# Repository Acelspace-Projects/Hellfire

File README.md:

<h1 align="center">
    <br>
    
    <br>
    <b>Hellfire</b>
</h3>

<h3 align="center">
    Ceci est un dépot pour le projet Hellfire utilisé pour le versionning et pour avoir des backups.
</h3>

<div class="badges" align="center">

</div>

---

### Description
Hellfire est un projet du club Acelspace.

### Liens
- [StabTraj](https://github.com/Acelspace-Projects/Hellfire/blob/main/Documentation/StabTraj/ST-(StabTraj)_Hellfire.xlsx)
- [Dossier de définition](https://github.com/Acelspace-Projects/Hellfire/blob/main/Documentation/DossierDeDefinition/DDD_Hellfire.pdf)
- [Dossier technique](https://github.com/Acelspace-Projects/Hellfire/blob/main/Documentation/DossierTechnique/DT_Hellfire.pdf)

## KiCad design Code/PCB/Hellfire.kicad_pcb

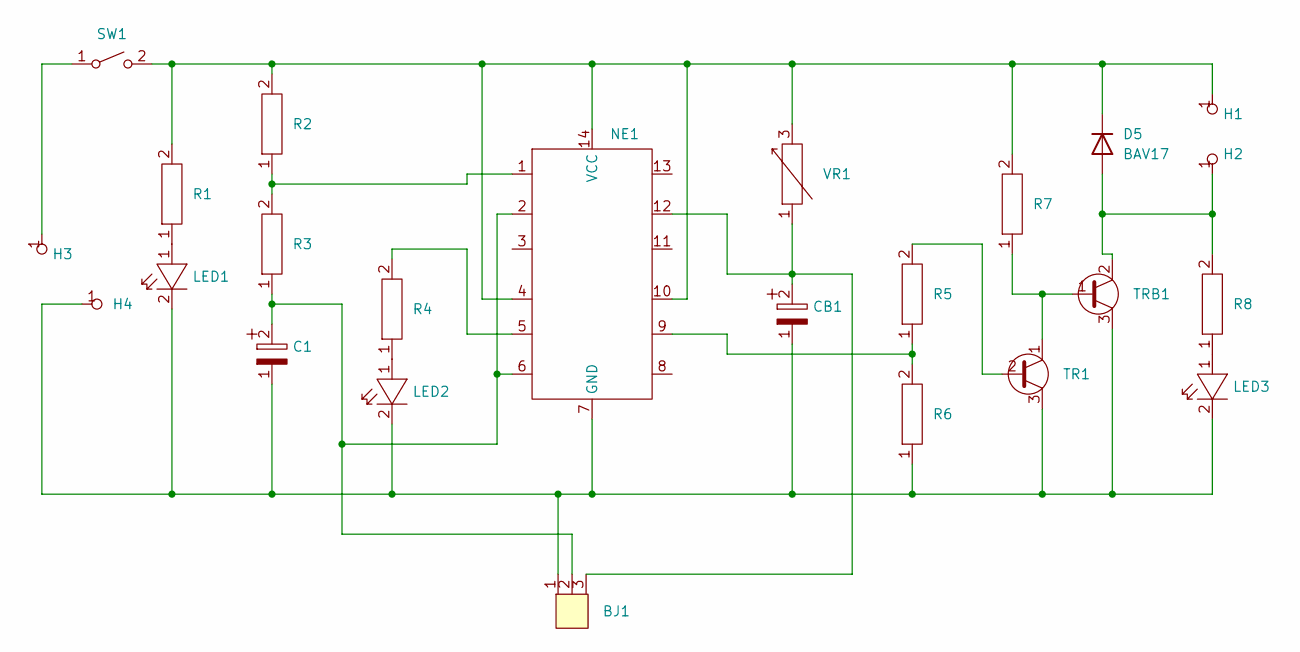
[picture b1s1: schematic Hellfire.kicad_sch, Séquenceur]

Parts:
BJ1: Jack
C1: Capacitor
CB1: Capacitor Big
D5: BAV17; D_DO-35_SOD27_P7.62mm_Horizontal
H1, H2, H3, H4: Via
LED1, LED2, LED3: LED
NE1: NE556
R1, R2, R3, R4, R5, R6, R7, R8: Resistor
SW1: Switch
TR1: Transistor
TRB1: Transistor Big
VR1: Variable Resistor

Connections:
unnamed: BJ1.2, C1.2, NE1.2, NE1.6, R3.1
unnamed: BJ1.3, CB1.2, NE1.12, VR1.1
unnamed: D5.2 (A), H2.1, R8.2, TRB1.2
unnamed: D5.1 (K), H1.1, NE1.4, NE1.10, NE1.14 (VCC), R1.2, R2.2, R7.2, SW1.2, VR1.3
unnamed: H3.1, SW1.1
unnamed: LED1.1, R1.1
unnamed: LED2.1, R4.1
unnamed: LED3.1, R8.1
unnamed: BJ1.1, C1.1, CB1.1, H4.1, LED1.2, LED2.2, LED3.2, NE1.7 (GND), R6.1, TR1.3, TRB1.3
unnamed: NE1.1, R2.1, R3.2
unnamed: NE1.5, R4.2
unnamed: NE1.9, R5.1, R6.2
unnamed: R5.2, TR1.2
unnamed: R7.1, TR1.1, TRB1.1

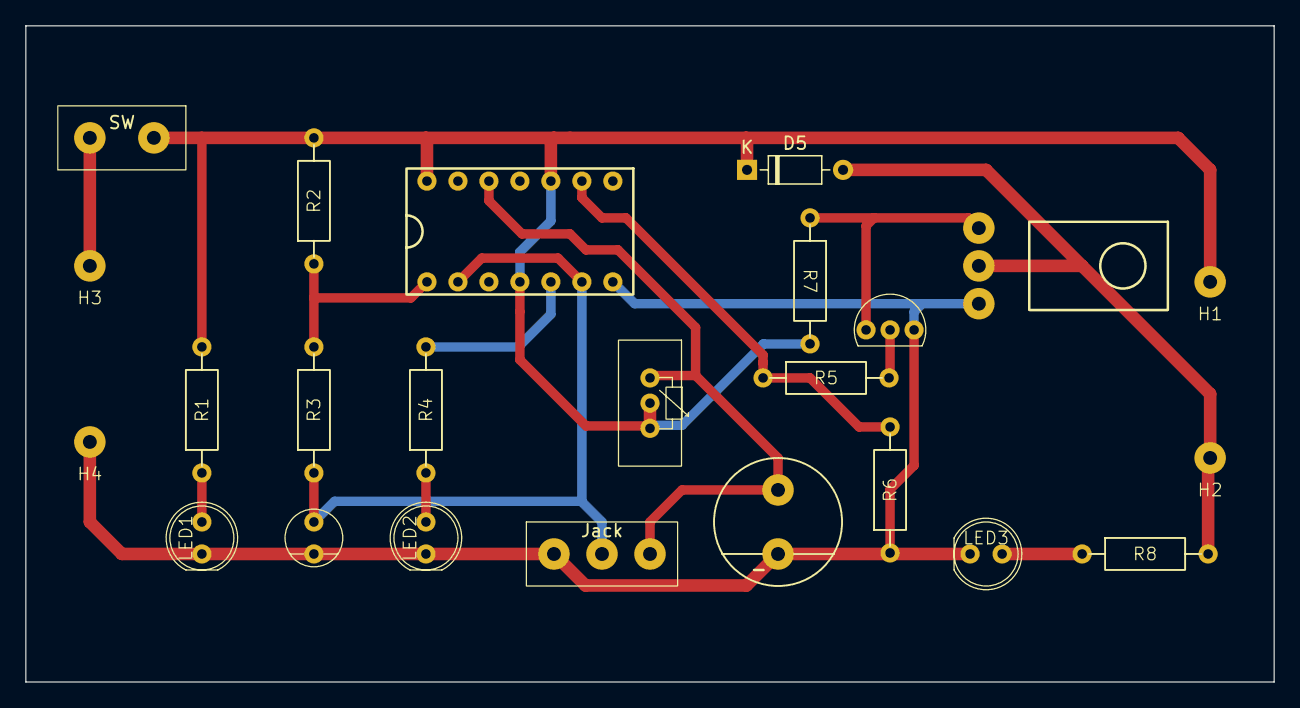
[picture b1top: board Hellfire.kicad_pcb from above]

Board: 2 copper layers, 99.1 x 52.1 mm, 24 parts (0 on the bottom side), 14 nets.

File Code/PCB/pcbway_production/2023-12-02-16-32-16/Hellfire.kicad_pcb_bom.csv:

designator,quantity,value,pack,mpn,mount_type
BJ1,1,~,Jack,,tht
C1,1,~,Capacitor,,tht
CB1,1,~,Capacitor Big,,tht
D5,1,BAV17,D_DO-35_SOD27_P7.62mm_Horizontal,,tht
"H1, H2, H3, H4",4,~,Via,,tht
"LED1, LED2, LED3",3,~,LED,,tht
NE1,1,~,NE556,,tht
"R1, R2, R3, R4, R5, R6, R7, R8",8,~,Resistor,,tht
SW1,1,~,Switch,,tht
TR1,1,~,Transistor,,tht
TRB1,1,~,Transistor Big,,tht
VR1,1,~,Variable Resistor,,tht

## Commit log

2024-01-27 Kicad modifications + components list update
2024-02-03 Hellfire+pcb update
2024-04-28 remove Minuterie PCB (to Nextcloud archive)
2024-04-28 Add boards-related instructions
2024-04-28 Update StabTraj
2024-05-07 zbeub
2024-05-23 Update lora feather code (add GPS)
2024-05-31 Update for debug
2024-06-29 Update code
2024-07-05 Update code and add Fritzing files
2024-07-09 Code updates
2024-07-25 Analyse 1
2024-08-31 Analyse 2
2024-11-05 Update graphs - results exploitation - calibration
2024-11-09 Add sensor documentation
2024-12-01 Update analysis
2024-12-01 Graphs.py cleanup
2024-12-01 Update graphs (BMP)
2024-12-22 GPS exploitation update
2024-12-24 Update graphs
2024-12-27 Reformat graph making
2025-01-01 Fix README.md links
2025-01-14 Use pandas for reading csv files
2025-03-15 Add BMP compensation calculations
2025-03-15 IMU 3 val moy
2025-05-25 Traduction des comentaires
2025-06-10 Final analysis update
